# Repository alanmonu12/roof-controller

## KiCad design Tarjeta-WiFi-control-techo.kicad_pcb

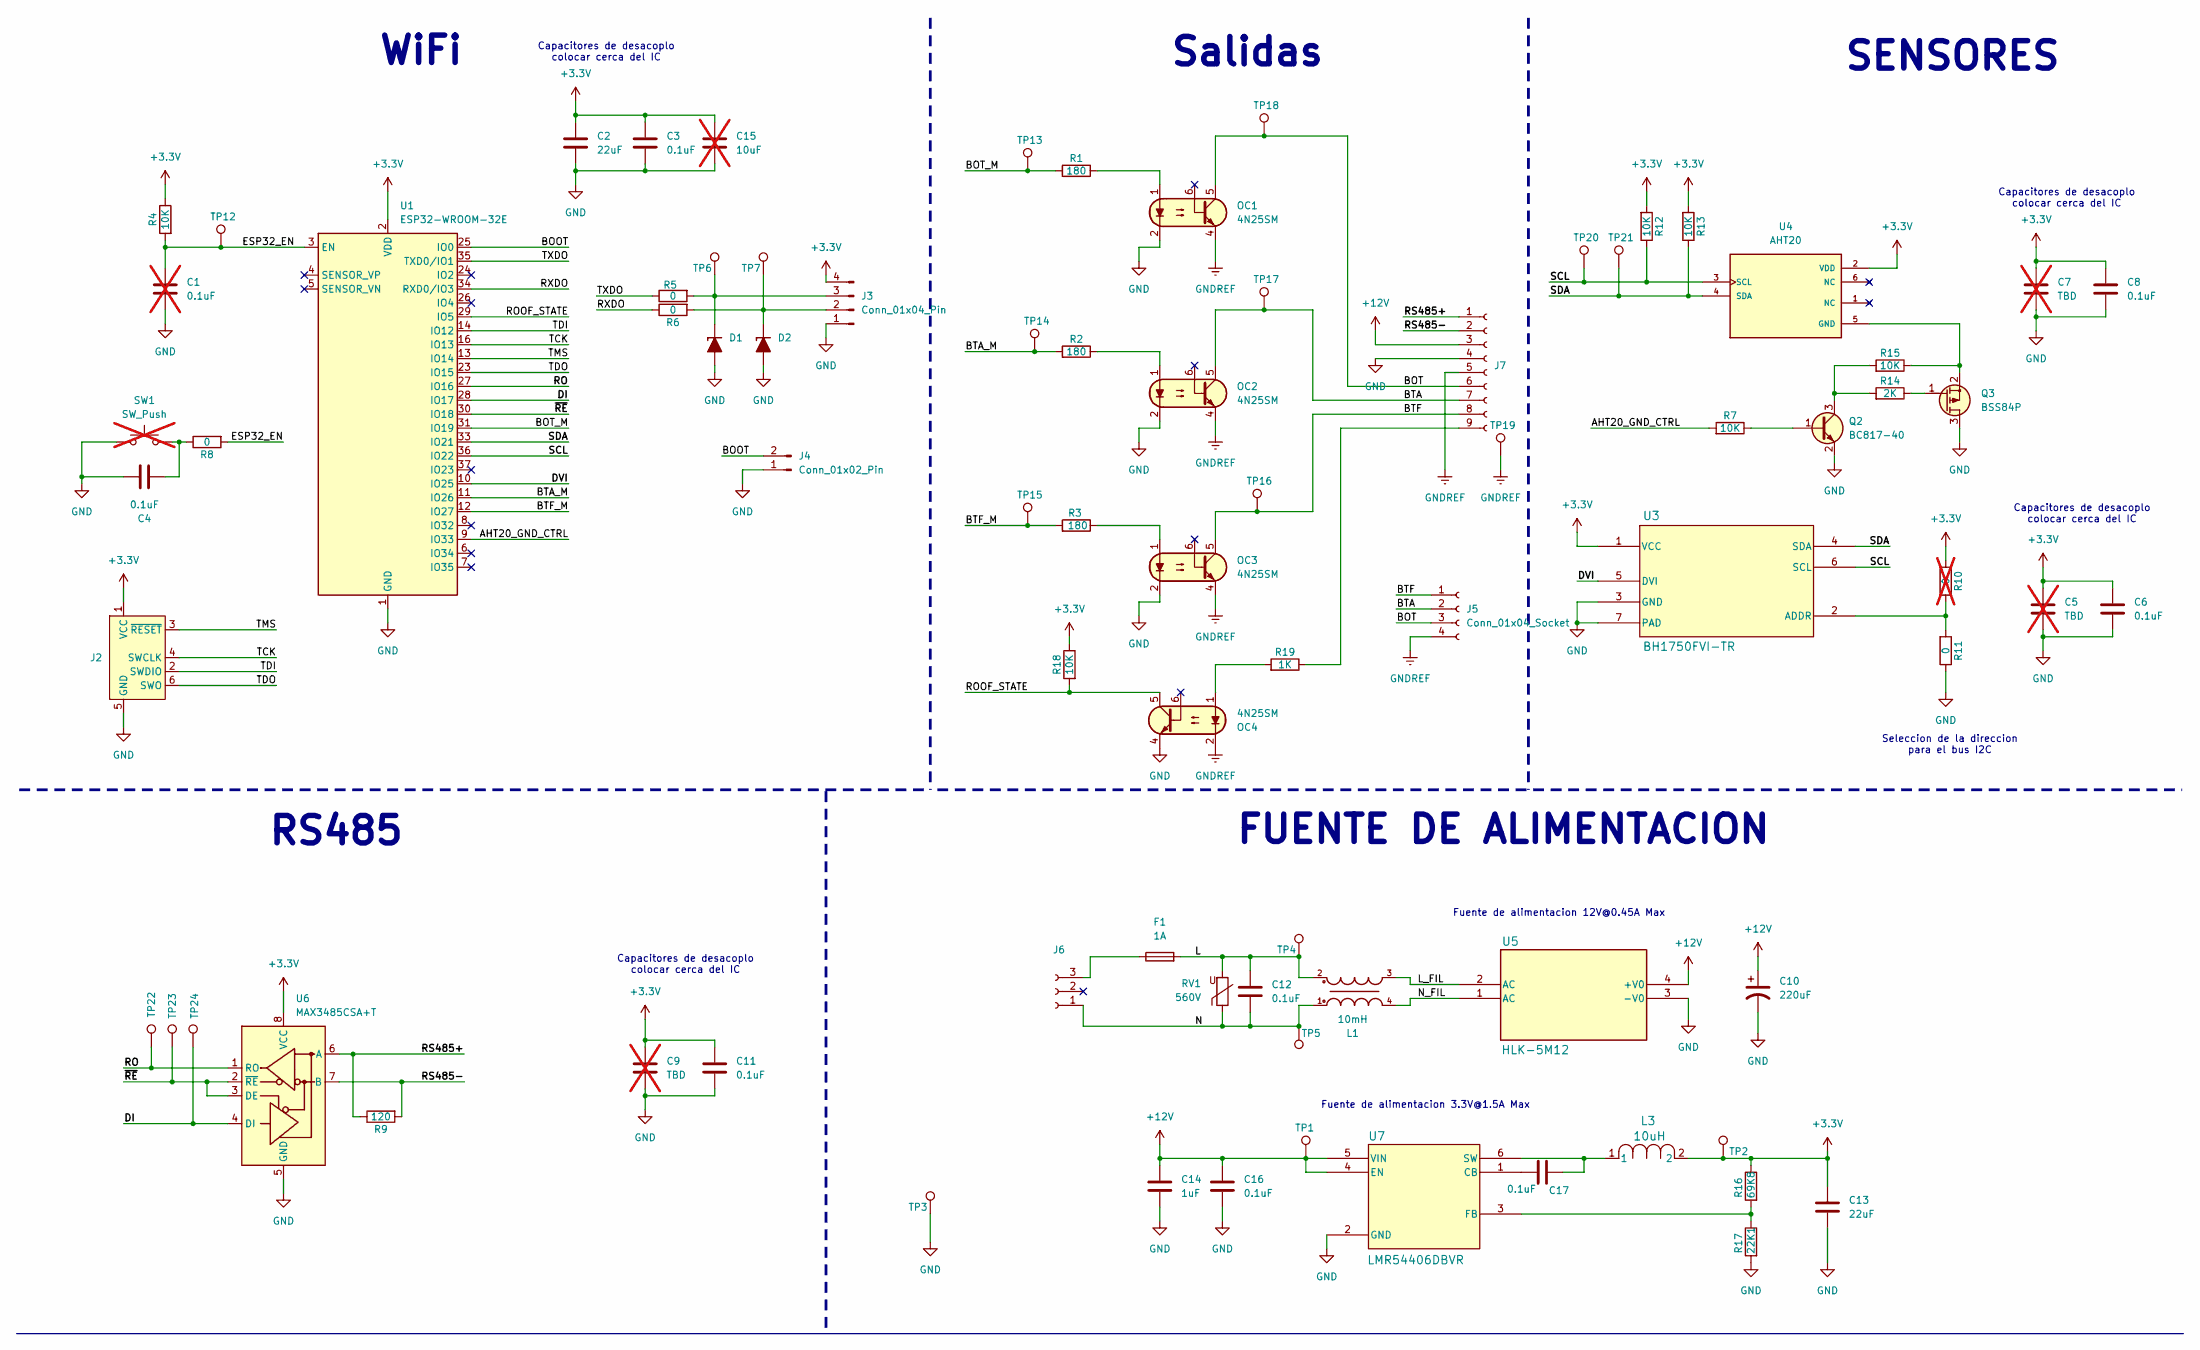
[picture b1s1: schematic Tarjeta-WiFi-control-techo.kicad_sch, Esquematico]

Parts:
C1: 0.1uF; C_0805_2012Metric; not fitted
C2, C13: 22uF; C_0805_2012Metric; MPN GRM21BZ71A226ME15L
C3, C4, C6, C8, C11, C16, C17: 0.1uF; C_0805_2012Metric; MPN GCD21BR71H104KA01L
C5, C7, C9: TBD; C_0805_2012Metric; not fitted
C10: 220uF; CP_Elec_5x3; MPN EEH-ZL1E221XV
C12: 0.1uF; C_Disc_D5.0mm_W2.5mm_P5.00mm; MPN GCD21BR71H104KA01L
C14: 1uF; C_0805_2012Metric; MPN GCM21BR71H105KA03L
C15: 10uF; C_0805_2012Metric; not fitted
D1, D2: PTVS5V0S1UTR; D_SOD-123F; MPN PTVS5V0S1UTR,115
F1: 1A; Fuseholder_Cylinder-5x20mm_Schurter_0031_8201_Horizontal_Op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; MPN 0031.8211
J2: Conn_ARM_SWD_TagConnect_TC2030-NL; Tag-Connect_TC2030-IDC-NL_2x03_P1.27mm_Vertical
J3: Conn_01x04_Pin; PinHeader_1x04_P2.54mm_Vertical
J4: Conn_01x02_Pin; PinHeader_1x02_P2.54mm_Vertical
J5: Conn_01x04_Socket; PhoenixContact_MC_1,5_4-G-3.81_1x04_P3.81mm_Horizontal; MPN 1803293
J6: Conn_01x03_Socket; PhoenixContact_MC_1,5_3-G-3.81_1x03_P3.81mm_Horizontal; MPN 1803280
J7: Conn_01x09_Socket; PhoenixContact_MC_1,5_9-G-3.81_1x09_P3.81mm_Horizontal; MPN 1803345
L1: 10mH; WE-CMB_XS; MPN 744821110
L3: 10uH; IND_05042100_WRE; MPN 74405042100
OC1, OC2, OC3, OC4: 4N25SM; SMDIP-6_W9.53mm; MPN 4N25SM
Q2: BC817-40; SOT-23; MPN BC817-40W,115
Q3: BSS84P; SOT-23; MPN BSS84PH6327XTSA2
R1, R2, R3: 180; R_0805_2012Metric; MPN RNCP0805FTD180R
R4, R7, R12, R13, R15, R18: 10K; R_0805_2012Metric; MPN RNCP0805FTD10K0
R5, R6, R8, R11: 0; R_0805_2012Metric; MPN RMCF0805ZT0R00
R9: 120; R_0805_2012Metric; MPN RNCF0805BTE120R
R10: 0; R_0805_2012Metric; not fitted
R14: 2K; R_0805_2012Metric; MPN RPC0805JT2K00
R16: 69K8; R_0805_2012Metric; MPN RK73H2ATTD6982F
R17: 22K1; R_0805_2012Metric; MPN RK73H2ATTD2212F
R19: 1K; R_0805_2012Metric; MPN RPC0805JT1K00
RV1: 560V; RV_Disc_D7mm_W3.4mm_P5mm; MPN MOV-10D561K
SW1: SW_Push; SW_Push_SPST_NO_Alps_SKRK; not fitted
TP1, TP2, TP3, TP4, TP5, TP6, TP7, TP12, TP13, TP14, TP15, TP16, TP17, TP18, TP19, TP20, TP21, TP22, TP23, TP24: TestPoint; TestPoint_Pad_D1.0mm
U1: ESP32-WROOM-32E; ESP32-WROOM-32D; MPN ESP32-WROOM-32E-H4
U3: BH1750FVI-TR; BH1750FVI-TR_ROM-M; MPN BH1750FVI-TR
U4: AHT20; PSON100P300X300X110-6N; PARTREV V1.0
U5: HLK-5M12; HLK-5Mxx_HLK; MPN HLK-5M12
U6: MAX3485CSA+T; SOIC-8_3.9x4.9mm_P1.27mm; MPN MAX3485CSA+T
U7: LMR54406DBVR; LMR54406DBVR_TEX; MPN LMR54406DBVR

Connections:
+3.3V: C2.1, C3.1, C5.1, C6.1, C7.1, C8.1, C9.1, C11.1, C13.1, C15.1, J2.1 (VCC), J3.4, L3.2, R4.2, R10.1, R12.1, R13.1, R16.2, R18.2, TP2.1, U1.2 (VDD), U3.1 (VCC), U4.2 (VDD), U6.8 (VCC)
+12V: C10.1, C14.1, C16.1, J7.3, TP1.1, U5.4 (+V0), U7.4 (EN), U7.5 (VIN)
/AHT20_GND_CTRL: R7.1, U1.9 (IO33)
/BOOT: J4.2, U1.25 (IO0)
/BOT: J5.3, J7.6, OC1.5, TP18.1
/BOT_M: R1.1, TP13.1, U1.31 (IO19)
/BTA: J5.2, J7.7, OC2.5, TP17.1
/BTA_M: R2.1, TP14.1, U1.11 (IO26)
/BTF: J5.1, J7.8, OC3.5, TP16.1
/BTF_M: R3.1, TP15.1, U1.12 (IO27)
/DI: TP24.1, U1.28 (IO17), U6.4 (DI)
/DVI: U1.10 (IO25), U3.5 (DVI)
/ESP32_EN: C1.1, R4.1, R8.1, TP12.1, U1.3 (EN)
/L: C12.1, F1.2, L1.2, RV1.2, TP4.1
/L_FIL: L1.3, U5.2 (AC)
/N: C12.2, J6.1, L1.1, RV1.1, TP5.1
/N_FIL: L1.4, U5.1 (AC)
/RO: TP22.1, U1.27 (IO16), U6.1 (RO)
/ROOF_STATE: OC4.5, R18.1, U1.29 (IO5)
/RS485+: J7.1, R9.2, U6.6 (A)
/RS485-: J7.2, R9.1, U6.7 (B)
/RXDO: R6.2, U1.34 (RXD0/IO3)
/SCL: R12.2, TP20.1, U1.36 (IO22), U3.6 (SCL), U4.3 (SCL)
/SDA: R13.2, TP21.1, U1.33 (IO21), U3.4 (SDA), U4.4 (SDA)
/TCK: J2.4 (SWCLK), U1.16 (IO13)
/TDI: J2.2 (SWDIO), U1.14 (IO12)
/TDO: J2.6 (SWO), U1.23 (IO15)
/TMS: J2.3 (~RESET), U1.13 (IO14)
/TXDO: R5.2, U1.35 (TXD0/IO1)
/~RE: TP23.1, U1.30 (IO18), U6.2 (~RE), U6.3 (DE)
GND: C1.2, C2.2, C3.2, C4.2, C5.2, C6.2, C7.2, C8.2, C9.2, C10.2, C11.2, C13.2, C14.2, C15.2, C16.2, D1.2 (A), D2.2 (A), J2.5 (GND), J3.1, J4.1, J7.4, OC1.2, OC2.2, OC3.2, OC4.4, Q2.2 (E), Q3.3 (D), R11.2, R17.1, SW1.1, TP3.1, U1.1 (GND), U1.15 (GND), U1.38 (GND), U1.39 (GND), U3.3 (GND), U3.7 (PAD), U5.3 (-V0), U6.5 (GND), U7.2 (GND)
GNDREF: J5.4, J7.5, OC1.4, OC2.4, OC3.4, OC4.2, TP19.1
unnamed: C4.1, R8.2, SW1.2
unnamed: D1.1 (K), J3.3, R5.1, TP6.1
unnamed: D2.1 (K), J3.2, R6.1, TP7.1
unnamed: F1.1, J6.3
unnamed: J7.9, R19.2
unnamed: OC1.1, R1.2
unnamed: OC2.1, R2.2
unnamed: OC3.1, R3.2
unnamed: OC4.1, R19.1
unnamed: Q2.1 (B), R7.2
unnamed: Q2.3 (C), R14.1, R15.1
unnamed: Q3.1 (G), R14.2
unnamed: Q3.2 (S), R15.2, U4.5 (GND)
unnamed: R10.2, R11.1, U3.2 (ADDR)
unnamed: C17.1, U7.1 (CB)
unnamed: R16.1, R17.2, U7.3 (FB)
unnamed: C17.2, L3.1, U7.6 (SW)

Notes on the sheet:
Capacitores de desacoplo colocar cerca del IC
FUENTE DE ALIMENTACION
SENSORES
Fuente de alimentacion 12V@0.45A Max
WiFi
Fuente de alimentacion 3.3V@1.5A Max
RS485
Seleccion de la direccion para el bus I2C
Salidas

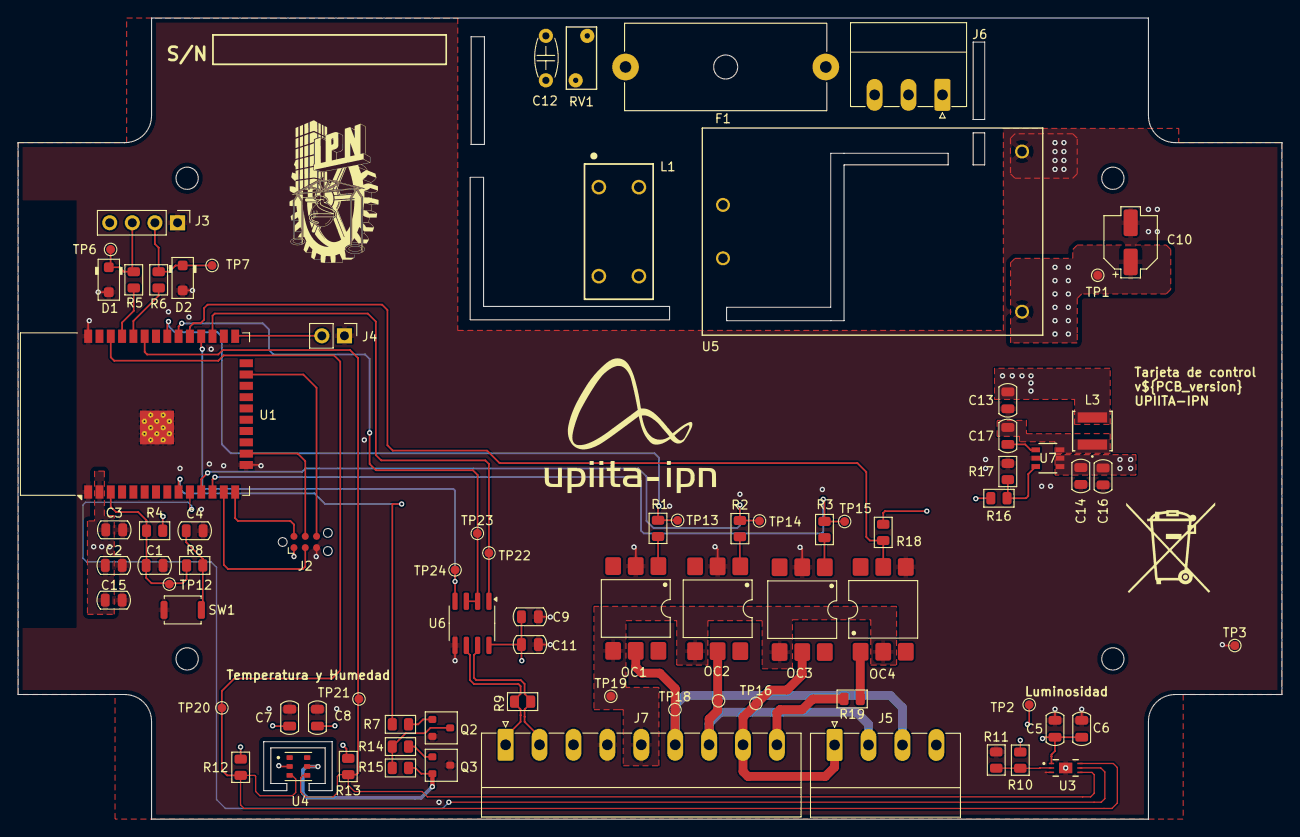
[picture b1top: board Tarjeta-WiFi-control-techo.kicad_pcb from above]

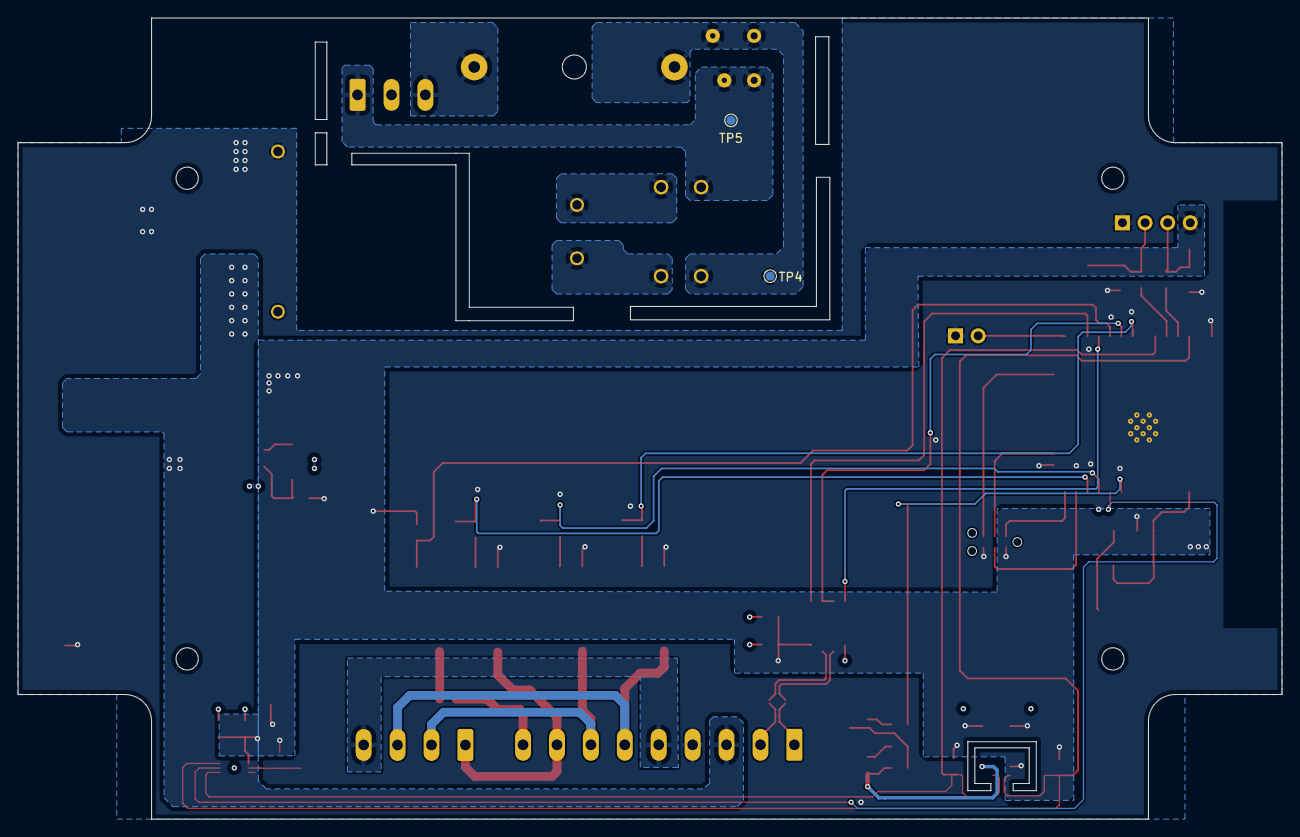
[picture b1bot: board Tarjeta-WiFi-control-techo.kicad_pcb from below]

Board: 4 copper layers, 142.0 x 90.0 mm, 81 parts (2 on the bottom side), 49 nets.

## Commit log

2025-06-11 Se agrego un conector para poder hacer uso del control manual
2025-07-18 final release
